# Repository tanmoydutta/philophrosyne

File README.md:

# Philophrosyne
A general purpose Bluetooth and WiFi enabled sensor board that has flexible interfaces for I2C, SPI Display and a SEN-54 seneor module.
The unit can be powered by USB-C connector or a LiPo battery. This module has built in battery charging circuit.
The model board - 

Primary purpose of this board is to interface with SEN-54 sensors. A housing compatible with containing the sensor unit as well as the board is designed.

The concept module with coer removed-

Below is the built module with the sensor and housing -

This is an OSHWA certified hardware - 
<p align="center">
  
</p>

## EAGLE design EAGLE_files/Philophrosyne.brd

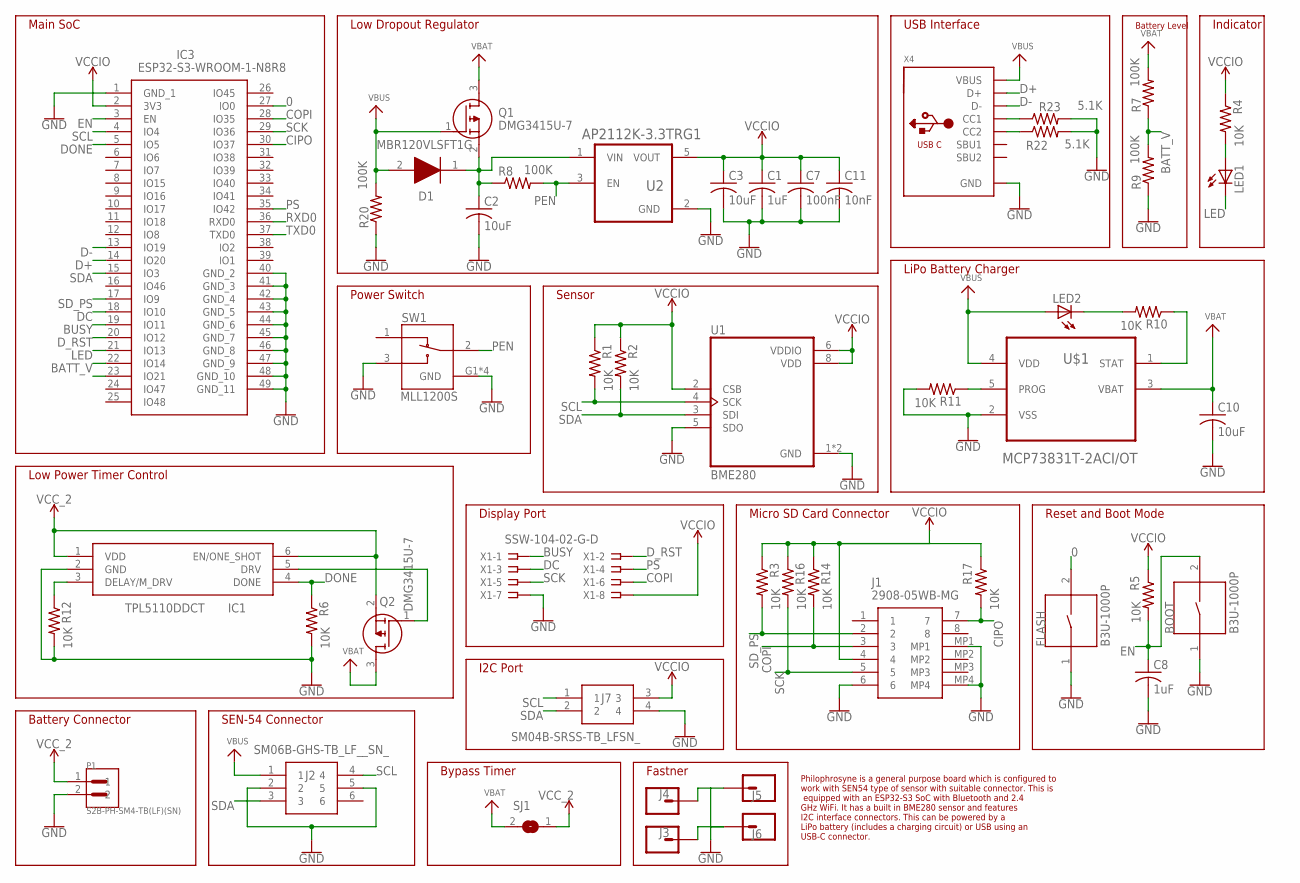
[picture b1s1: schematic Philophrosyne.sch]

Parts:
BOOT: B3U-1000P; SW_B3U-1000P
C1, C8: 1uF; C0402
C2, C3, C10: 10uF; C0402
C7: 100nF; C0402
C11: 10nF; C0402
D1: MBR120VLSFT1G; SODFL3616X98N
FLASH: B3U-1000P; SW_B3U-1000P
IC1: TPL5110DDCT; SOT95P280X110-6N
IC3: ESP32-S3-WROOM-1-N8R8; ESP32S3WROOM1N8R8
J1: 2908-05WB-MG; 290805WBMG
J2: SM06B-GHS-TB_LF__SN_; SM06B-GHS-TB
J3, J4, J5, J6: CONN_01PTH_2MM; 1X01_2MM
J7: SM04B-SRSS-TB_LFSN_; SM04B-SRSS-TB(LFSN)
LED1, LED2: LEDCHIP-LED0603; CHIP-LED0603
P1: S2B-PH-SM4-TB(LF)(SN); JST_S2B-PH-SM4-TB(LF)(SN)
Q1, Q2: DMG3415U-7; SOT96P240X100-3N
R1, R2, R3, R4, R5, R6, R10, R11, R12, R14, R16, R17: 10K; R0402
R7, R8, R9, R20: 100K; R0402
R22, R23: 5.1K; R0402
SJ1: SJ
SW1: MLL1200S; SW_MLL1200S
U1: BME280; PSON65P250X250X100-8N
U2: AP2112K-3.3TRG1; SOT95P285X140-5N
U$1: MCP73831T-2ACI/OT; SOT95P280X145-5N
X1: SSW-104-02-G-D
X4: MICROBUILDER_USB_C; MICROBUILDER_USB_C_CUSB31-CFM2AX-01-X

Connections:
0: FLASH.2, IC3.27 (IO0)
BATT_V: IC3.22 (IO14), R7.1, R9.2
BUSY: IC3.19 (IO11), X1.1
CIPO: IC3.30 (IO37), J1.7, R17.2
COPI: IC3.28 (IO35), J1.3, R14.2, X1.6
D+: IC3.14 (IO20), X4.A6 (D+), X4.B6 (D+)
D-: IC3.13 (IO19), X4.A7 (D-), X4.B7 (D-)
DC: IC3.18 (IO10), X1.3
DONE: IC1.4 (DONE), IC3.5 (IO5), R6.1
D_RST: IC3.20 (IO12), X1.2
EN: BOOT.2, C8.1, IC3.3 (EN), R5.2
GND: BOOT.1, C1.2, C2.2, C3.2, C7.2, C8.2, C10.2, C11.2, FLASH.1, IC1.2 (GND), IC3.1 (GND_1), IC3.40 (GND_2), IC3.41 (GND_3), IC3.42 (GND_4), IC3.43 (GND_5), IC3.44 (GND_6), IC3.45 (GND_7), IC3.46 (GND_8), IC3.47 (GND_9), IC3.48 (GND_10), IC3.49 (GND_11), J1.6, J1.MP1, J1.MP4, J2.2, J2.5, J3.1, J4.1, J5.1, J6.1, J7.4, P1.2, R6.2, R9.1, R11.2, R12.2, R20.1, R22.2, R23.2, SW1.3, SW1.G1 (GND), SW1.G2 (GND), SW1.G3 (GND), SW1.G4 (GND), U1.1 (GND), U1.5 (SDO), U1.7 (GND), U2.2 (GND), U$1.2 (VSS), X1.7, X4.A1B12 (GND), X4.B1A12 (GND)
LED: IC3.21 (IO13), LED1.C
unnamed: C2.1, D1.1 (K), Q1.2 (S), R8.1, U2.1 (VIN)
unnamed: R22.1, X4.B5 (CC2)
unnamed: R11.1, U$1.5 (PROG)
unnamed: R23.1, X4.A5 (CC1)
unnamed: LED1.A, R4.2
unnamed: IC1.5 (DRV), Q2.1 (G)
unnamed: R10.1, U$1.1 (STAT)
unnamed: LED2.C, R10.2
unnamed: IC1.3 (DELAY/M_DRV), R12.1
PEN: R8.2, SW1.2, U2.3 (EN)
PS: IC3.35 (IO42), X1.4
RXD0: IC3.36 (RXD0)
SCK: IC3.29 (IO36), J1.5, R16.2, X1.5
SCL: IC3.4 (IO4), J2.4, J7.1, R1.2, U1.4 (SCK)
SDA: IC3.15 (IO3), J2.3, J7.2, R2.2, U1.3 (SDI)
SD_PS: IC3.17 (IO9), J1.2, R3.2
TXD0: IC3.37 (TXD0)
VBAT: C10.1, Q1.3 (D), Q2.3 (D), R7.2, SJ1.2, U$1.3 (VBAT)
VBUS: D1.2 (A), J2.1, LED2.A, Q1.1 (G), R20.2, U$1.4 (VDD), X4.A4B9 (VBUS), X4.B4A9 (VBUS)
VCCIO: C1.1, C3.1, C7.1, C11.1, IC3.2 (3V3), J1.4, J7.3, R1.1, R2.1, R3.1, R4.1, R5.1, R14.1, R16.1, R17.1, U1.2 (CSB), U1.6 (VDDIO), U1.8 (VDD), U2.5 (VOUT), X1.8
VCC_2: IC1.1 (VDD), IC1.6 (EN/ONE_SHOT), P1.1, Q2.2 (S), SJ1.1

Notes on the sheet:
Main SoC
Low Dropout Regulator
Low Power Timer Control
Power Switch
Sensor
Display Port
Battery Connector
SEN-54 Connector
I2C Port
Bypass Timer
Fastner
Micro SD Card Connector
USB Interface
Battery Level
Indicator
LiPo Battery Charger
Reset and Boot Mode
Philophrosyne is a general purpose board which is configured to work with SEN54 type of sensor with suitable connector. This is equipped with an ESP32-S3 SoC with Bluetooth and 2.4 GHz WiFi. It has a built in BME280 sensor and features I2C interface connectors. This can be powered by a LiPo battery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

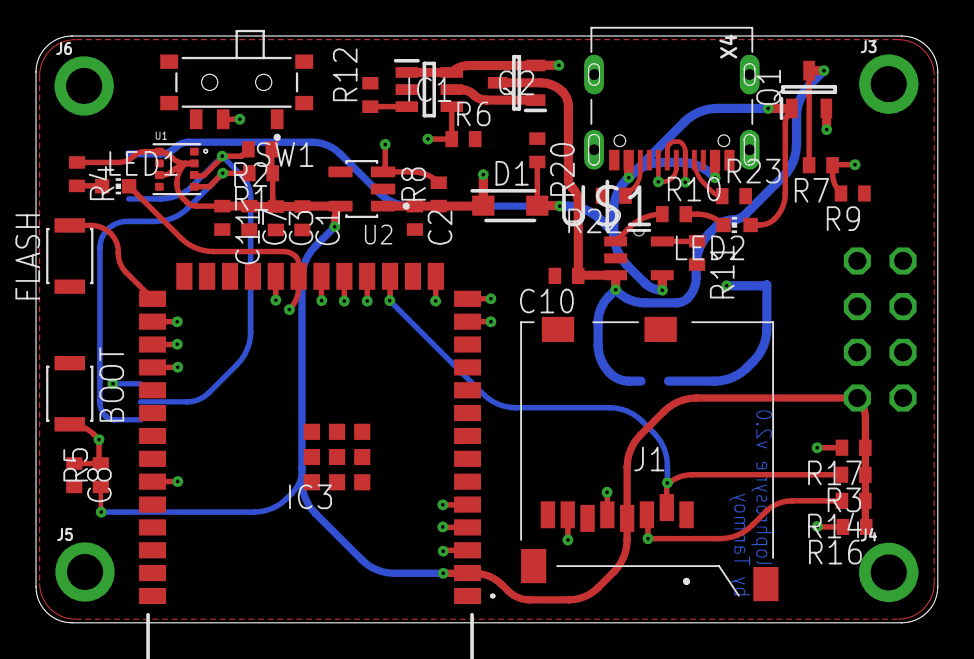
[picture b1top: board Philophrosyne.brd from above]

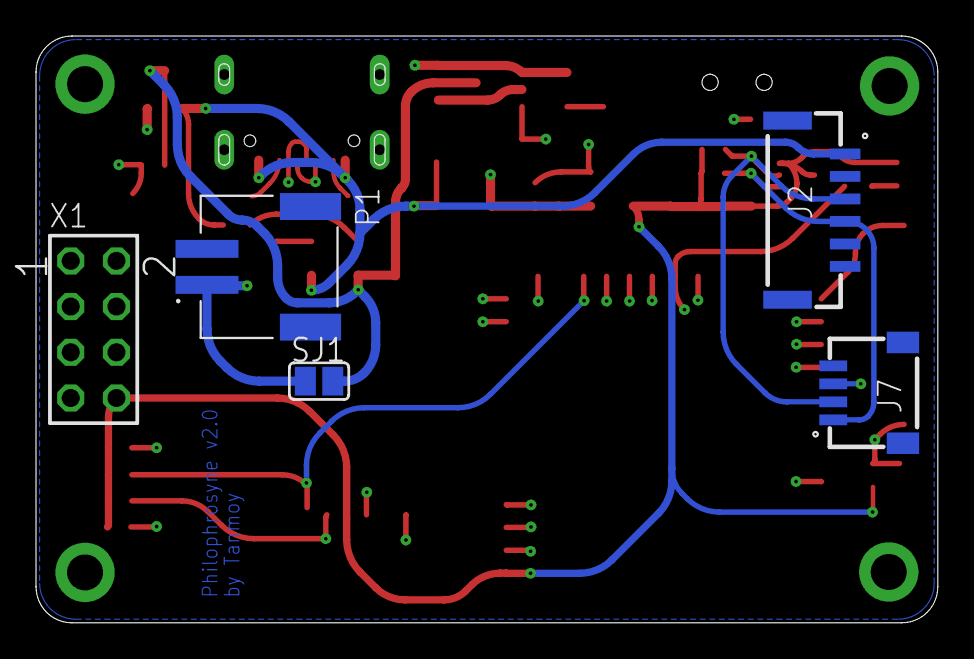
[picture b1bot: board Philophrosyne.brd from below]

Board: 4 copper layers, 50.1 x 32.6 mm, 49 parts (5 on the bottom side), 32 nets.

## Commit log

2025-06-06 Adding files
2025-06-12 Adding OSHWA mark
2025-06-23 Adding a sample sketch

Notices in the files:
parts and their libraries:
SparkFun-Connectors: Licensing: Creative Commons ShareAlike 4.0 International - https://creativecommons.org/licenses/by-sa/4.0
